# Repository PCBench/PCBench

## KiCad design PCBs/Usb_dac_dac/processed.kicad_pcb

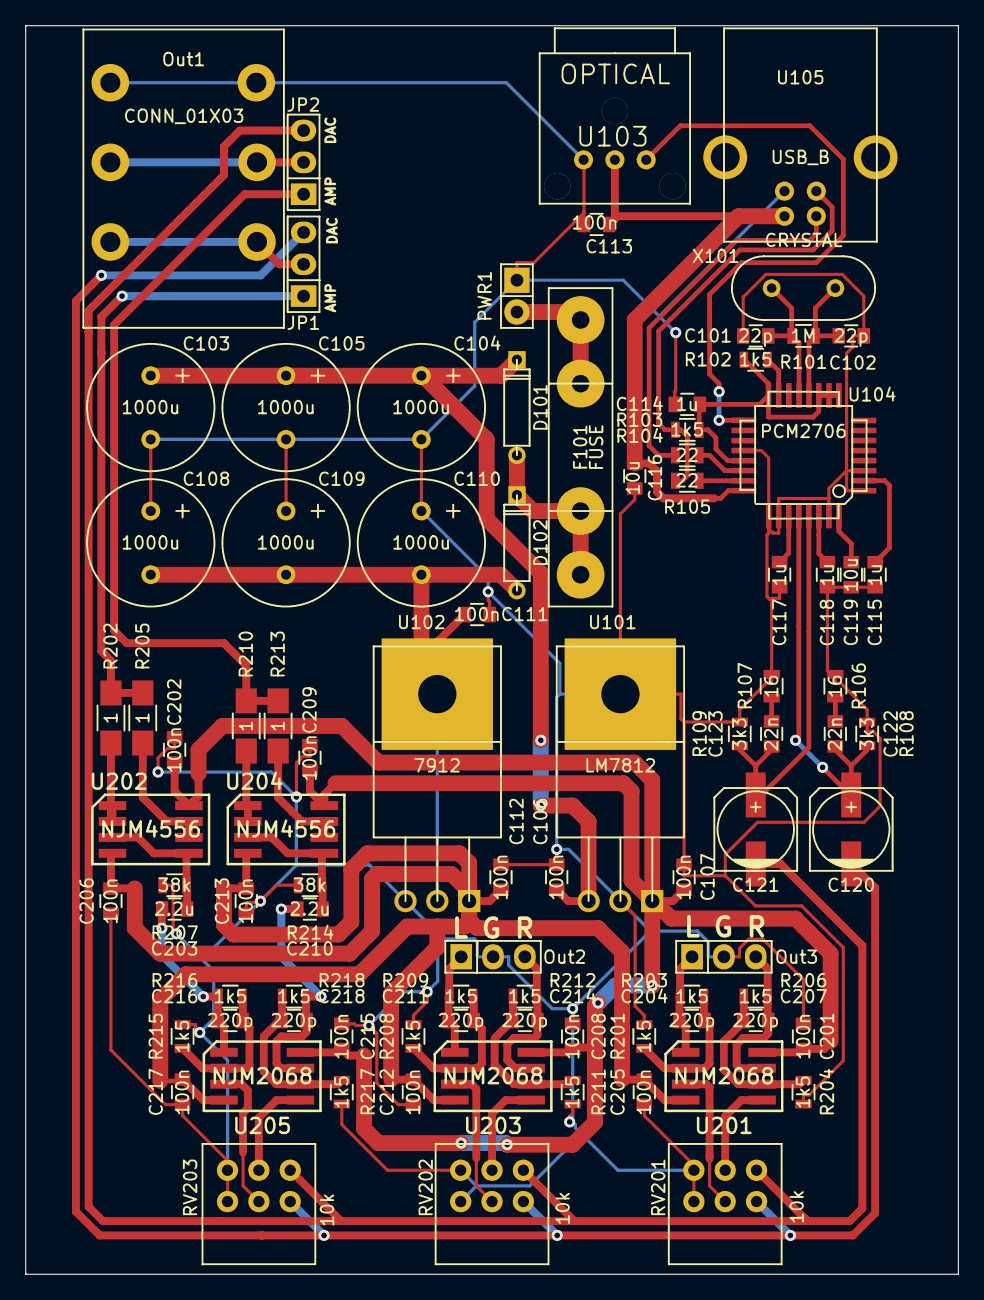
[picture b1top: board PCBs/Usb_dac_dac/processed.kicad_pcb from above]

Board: 2 copper layers, 74.4 x 99.6 mm, 91 parts (0 on the bottom side), 55 nets.

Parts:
C101, C102: 22p; C_0805
C103, C104, C105, C108, C109, C110: 1000u; Elko_vert_20x10mm_RM5
C106, C107, C111, C112, C113, C201, C202, C205, C206, C208, C209, C212, C213, C215, C217: 100n; C_0805
C114, C115, C117, C118: 1u; C_0805
C116, C119: 10u; C_0805
C120, C121: 100u; c_elec_6.3x5.3
C122, C123: 22n; C_0805
C203, C210: 2.2u; C_0805
C204, C207, C211, C214, C216, C218: 220p; C_0805
D101, D102: DIODE; D3
F101: FUSE; FUSE5-20
JP1, JP2: CONN_01X03; Pin_Header_Straight_1x03
Out1: CONN_01X03; SIKA
Out2, Out3: CONN_01X03; Pin_Header_Straight_1x03
PWR1: CONN_01X02; Pin_Header_Straight_1x02
R101: 1M; R_0805
R102, R103, R201, R203, R204, R206, R208, R209, R211, R212, R215, R216, R217, R218: 1k5; R_0805
R104, R105: 22; R_0805
R106, R107: 16; R_0805
R108, R109: 3k3; R_0805
R202, R205, R210, R213: 1; R_1206_HandSoldering
R207, R214: 38k; R_0805
RV201, RV202, RV203: 10k; RK097
U101: LM7812; TO220
U102: 7912; TO220
U103: OPTICAL; KFOX
U104: PCM2706; TQFP-32
U105: USB_B
U201, U203, U205: NJM2068; SOIC 8
U202, U204: NJM4556; SOIC 8
X101: CRYSTAL; HC-49V

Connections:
3V3: C114.2, R102.2, R103.2, U104.9, U104.10, U104.11, U104.16, U104.21
+5V: C113.2, C116.1, U103.2, U104.24, U105.1
+12V: C107.1, C201.2, C202.2, C208.2, C209.2, C215.2, U101.3, U201.8, U202.8, U203.8, U204.8, U205.8
-12V: C112.2, C205.2, C206.2, C212.2, C213.2, C217.2, U102.3, U201.4, U202.4, U203.4, U204.4, U205.4
/Buffers/Left out 1: JP1.1, R202.2, R205.2
/Buffers/Left out 2: C211.2, Out2.1, R209.2, U203.1
/Buffers/Left out 3: C204.2, Out3.1, R203.2, U201.1
/Buffers/Left_in: C120.2, JP1.3, RV201.3, RV202.3, RV203.3
/Buffers/Right out 1: JP2.1, R210.2, R213.2
/Buffers/Right out 2: C214.2, Out2.3, R212.2, U203.7
/Buffers/Right out 3: C207.2, Out3.3, R206.2, U201.7
/Buffers/Right_in: C121.2, JP2.3, RV201.6, RV202.6, RV203.6
AGND: C101.2, C102.2, C103.2, C104.2, C105.2, C106.2, C107.2, C108.1, C109.1, C110.1, C111.1, C112.1, C113.1, C114.1, C115.2, C116.2, C117.2, C118.2, C119.2, C201.1, C202.1, C205.1, C206.1, C208.1, C209.1, C212.1, C213.1, C215.1, C217.1, Out1.1, Out2.2, Out3.2, PWR1.1, R106.2, R107.2, R108.2, R109.2, R201.2, R204.2, R207.2, R208.2, R211.2, R214.2, R215.2, R217.2, RV201.1, RV201.4, RV202.1, RV202.4, RV203.1, RV203.4, U101.2, U102.1, U103.1, U104.1, U104.3, U104.20, U104.25, U104.26, U104.31, U105.4
unnamed: C101.1, R101.2, U104.13, X101.2
unnamed: C102.1, R101.1, U104.12, X101.1
unnamed: C103.1, C104.1, C105.1, C106.1, D101.2, U101.1
unnamed: C108.2, C109.2, C110.2, C111.2, D102.1, U102.2
unnamed: C115.1, U104.2
unnamed: C117.1, U104.27
unnamed: C118.1, U104.30
unnamed: C119.1, U104.32
unnamed: C120.1, C122.1, R108.1, U104.28
unnamed: C121.1, C123.1, R109.1, U104.29
unnamed: C122.2, R106.1
unnamed: C123.2, R107.1
unnamed: C203.1, C216.2, R216.2, U205.1
unnamed: C203.2, R207.1, U202.3, U202.5
unnamed: C204.1, R201.1, R203.1, U201.2
unnamed: C207.1, R204.1, R206.1, U201.6
unnamed: C210.1, C218.2, R218.2, U205.7
unnamed: C210.2, R214.1, U204.3, U204.5
unnamed: C211.1, R208.1, R209.1, U203.2
unnamed: C214.1, R211.1, R212.1, U203.6
unnamed: C216.1, R215.1, R216.1, U205.2
unnamed: C218.1, R217.1, R218.1, U205.6
unnamed: D101.1, D102.2, F101.2
unnamed: F101.1, PWR1.2
unnamed: JP1.2, Out1.3
unnamed: JP2.2, Out1.2
unnamed: R102.1, U104.15
unnamed: R103.1, R105.2, U105.3
unnamed: R104.1, U104.22
unnamed: R104.2, U105.2
unnamed: R105.1, U104.23
unnamed: R202.1, U202.1, U202.2
unnamed: R205.1, U202.6, U202.7
unnamed: R210.1, U204.1, U204.2
unnamed: R213.1, U204.6, U204.7
unnamed: RV201.2, U201.3
unnamed: RV201.5, U201.5
unnamed: RV202.2, U203.3
unnamed: RV202.5, U203.5
unnamed: RV203.2, U205.3
unnamed: RV203.5, U205.5
unnamed: U103.3, U104.17

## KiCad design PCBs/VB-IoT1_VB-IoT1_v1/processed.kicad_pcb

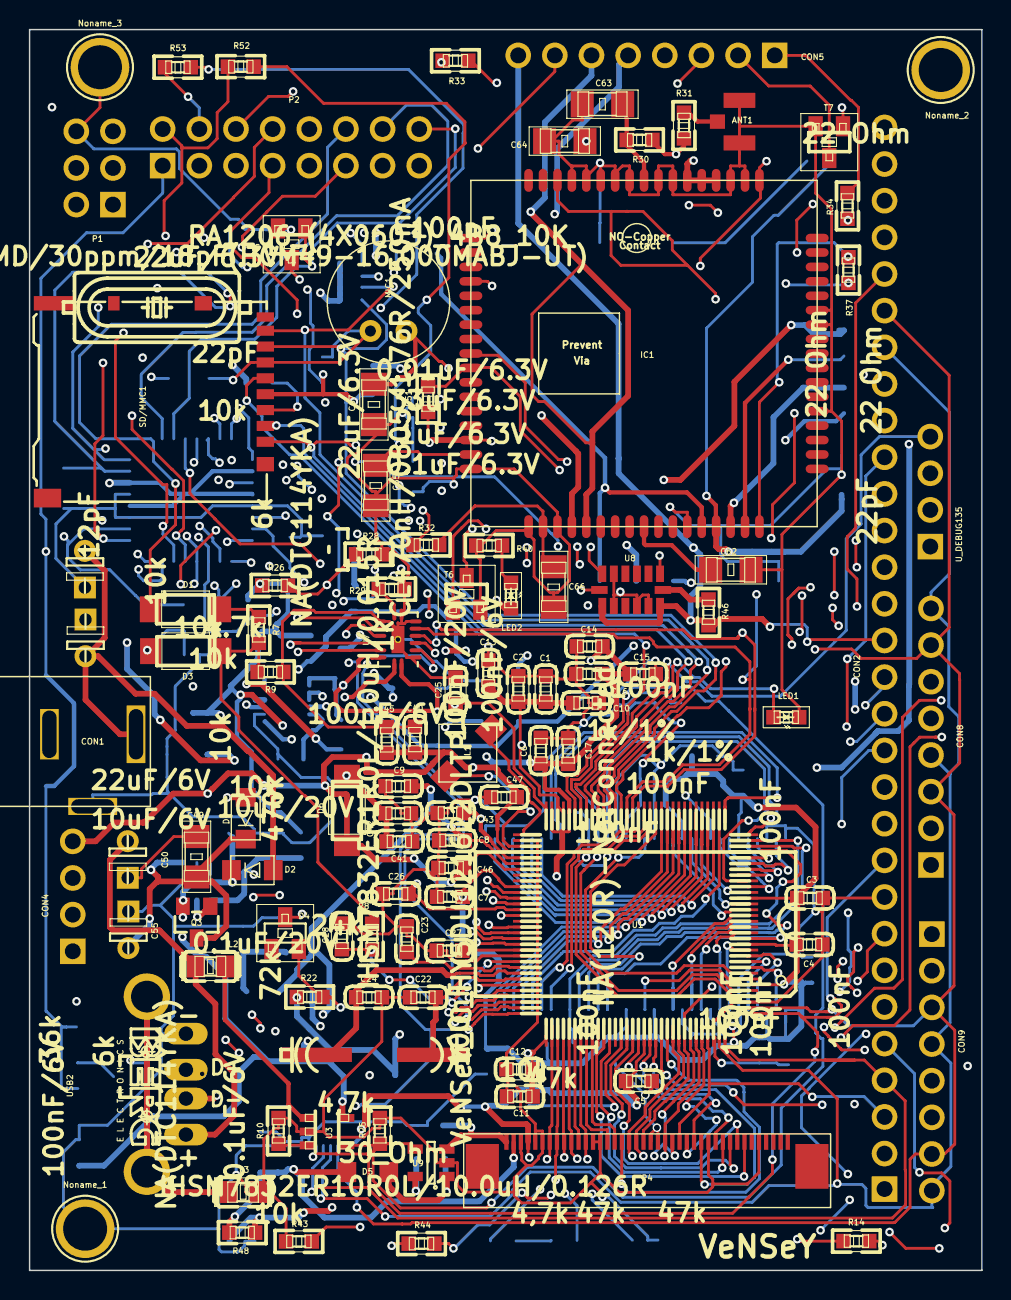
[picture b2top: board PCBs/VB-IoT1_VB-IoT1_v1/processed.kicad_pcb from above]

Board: 4 copper layers, 66.0 x 86.0 mm, 178 parts (0 on the bottom side), 195 nets.

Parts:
ANT1: 1909763-1; U.FL_CON_1909763-1
C1, C2, C3, C4, C5, C6, C11, C15, C19, C23, C25, C26, C43, C47: 0.1uF/6.3V; RCL_C0603_DWS
C7, C12, C16, C20, C27, C42, C45: 1uF/6.3V; RCL_C0603_DWS
C8, C29, C44: 22uF/6.3V; RCL_C0603_DWS
C9: 0.1uF; RCL_C0603_DWS
C10, C14, C18, C46: 0.01uF/6.3V; RCL_C0603_DWS
C13, C17, C21, C28, C40, C41: 33uF/6.3V; RCL_C0603_DWS
C22, C24: 10pF; RCL_C0603_DWS
C30, C31, C32, C33, C34, C35, C36, C37, C38, C39: 100nF; RCL_C0603_DWS
C48, C62, C65, C70, C71: 100nF/6V; RCL_C1206
C49, C52: 10uF/20V; RCL_C1206
C50: 100uF/16V/105C; RCL_E2_5-6_3
C51: 0.1uF/6V; RCL_C1206
C53, C54, C55: 220uF/10V/105C; RCL_E2_5-6_3
C56: 0.1uF/20V; RCL_C1206
C57: 10uF/6V; RCL_C1206
C58: 22uF/6V; RCL_C1206
C59: 100nF/20V; RCL_C1206
C60: 12pF; RCL_C1206
C61, C69: 22pF; RCL_C1206
C63, C64: --nF; RCL_C1206
C66, C67: 33pF; RCL_C1206
C68: 100nF; RCL_C1206
CON1: YDJ-1136; YDJ-1134-36
CON2: NA(HN1X30); PENKO_HN1X30
CON4: PENKO_CON4HN1X4; PENKO_HN1X4
CON5, CON8, CON9: PENKO_CON8HN1X8; PENKO_HN1X8
D1, D3, D6: 1N5819/SS14; GOGO_MLL-41
D2, D5, D7: SS2FL3; DO-219AB-SMF
D4: BAT54C; SEMICON-SMD-IPC_SOT23C
IC1: SIM900
IC2: ATMEGA328P-A; TQFP-32_7x7mm_Pitch0.8mm
L1: CDRH3D28NP-150N
L2, L3: FB0805/600R/2A; RCL_L0805_5MIL_DWS
L4: CL470nH/0805/1.76R/250mA; RCL_L0805_5MIL_DWS
L5: IHSM7832ER10R0L/10.0uH/0.126R; RCL_L0805_5MIL_DWS
L6: IHSM7832ER1R0L/1.0uH/0.015R; RCL_L0805_5MIL_DWS
LED1, LED2: GREEN(0603); DOUBLE-SIDE_LED-0603
MIC1: CEM-C9745JAD462P2.54R; ELECTRET_MIC
Noname_1, Noname_2, Noname_3: 1pin
P1: CONN_02X03; PENKO_HN2x3
P2: CONN_02X08; PENKO_HN2x8
P3: MOLEX_503480-0800; molex8-FCP
P4: TE_CONNECTIVITY_4-1734592-0; teConn40-FCP
Q1: Q24.000MHz/HC-49SM/SMD/20ppm/20pF; CRYSTAL_HC49_SMD2_THIN
Q2: Q16.000MHz/HCM49/SMD/30ppm/18pF(HCM49-16.000MABJ-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; CRYSTAL_HC49_SMD2_THIN
Q3: FDN306P; SUPERSOT-3
Q4: SQ2309ES; SOT23GDS
R1, R47: 6k; RCL_R0603_5MIL_DWS
R2: 36k; RCL_R0603_5MIL_DWS
R3, R4, R5, R7, R10, R16, R20, R21, R25, R39, R45, R46: 10k; RCL_R0603_5MIL_DWS
R6, R22: 4.7k; RCL_R0603_5MIL_DWS
R8, R40, R41: 1k; RCL_R0603_5MIL_DWS
R9: 100k; RCL_R0603_5MIL_DWS
R11, R12: 4,7k; RCL_R0603_5MIL_DWS
R13, R15, R42, R43, R44: 47k; RCL_R0603_5MIL_DWS
R14: NA(47k); RCL_R0603_5MIL_DWS
R17: NA(120R)-NotConnected; RCL_R0603_5MIL_DWS
R18, R19: 1k/1%; RCL_R0603_5MIL_DWS
R23: 24k; RCL_R0603_5MIL_DWS
R24: 72k; RCL_R0603_5MIL_DWS
R26: 768k; RCL_R0603_5MIL_DWS
R27: 470k; RCL_R0603_5MIL_DWS
R28: 137k; RCL_R0603_5MIL_DWS
R29, R51: 1K; RCL_R0603_5MIL_DWS
R30, R31: 0 Ohm; RCL_R0603_5MIL_DWS
R32: 33 Ohm; RCL_R0603_5MIL_DWS
R33, R34: 300 Ohm; RCL_R0603_5MIL_DWS
R35, R36, R38: 22 Ohm; RCL_R0603_5MIL_DWS
R37: 10K; RCL_R0603_5MIL_DWS
R48: 150k; RCL_R0603_5MIL_DWS
R50: 30_Ohm; RCL_R0603_5MIL_DWS
R52, R53: 2k; RCL_R0603_5MIL_DWS
R-MAT1: RA1206_(4X0603)_4B8_10K; OLIMEX_DISCRET_R_MATRIX_4
SD/MMC1: DM3AT-SF-PEJM5; HIROSE-MICROSD-DM3AT-SF_nooli
SIM1: Molex912283001; 91228-3001
T1, T5, T6, T7, T8: NA(DTC114YKA); OLIMEX_DISCRET_SOT-23
U1: MCIMX233CAG4C; OLIMEX_IC_TQFP128LD
U2: VeNSeY_IC_HY5DU121622DLTP-J; OLIMEX_IC_66TSOP-II
U3: SY6280; OLIMEX_IC_SOT23-5
U4: LTC4412
U5: TPS63020; VSON-14
U6: LM317AEMP; SOT223
U7: 74AVC4TD245; DHVQFN-16_2.5x3.5mm_Pitch0.5mm
U8: ADXL345; LGA14
U9: FAN5331SX; SOT-23-5
USB2: OLIMEX_CONNECTORS_USB_SHIELD; OLIMEX_CONNECTORS_USB_PN87520_DEV_PTH
U_DEBUG135: HN1X4; PENKO_HN1X4

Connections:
3V3_MODEM: C71.2, CON8.2, CON8.6, CON9.2, CON9.6, IC1.55, IC1.56, IC1.57, L5.2, LED2.A, Q4.D, R33.2, R34.2, U9.5
3V3_MODEM_ON: IC2.12, T8.1
3v3_Perm+: C58.1, C70.1, CON2.16, CON5.8, IC2.4, IC2.6, IC2.18, IC2.20, P1.2, Q4.S, R4.1, R5.1, R26.2, R27.2, R39.2, R46.1, U5.4, U8.1, U8.6
5V_Converter_IN: C48.1, C52.1, D2.1, Q3.S, U3.5, U4.6, U6.3
5V_IN: C8.1, C9.1, C56.1, CON2.1, R23.2, U1.102, U6.2
/A0: U1.76, U2.29
/A1: U1.75, U2.30
/A2: U1.74, U2.31
/A3: U1.73, U2.32
/A4: U1.72, U2.35
/A5: U1.71, U2.36
/A6: U1.70, U2.37
/A7: U1.69, U2.38
/A8: U1.68, U2.39
/A9: U1.67, U2.40
/A10: U1.66, U2.28
/A11: U1.65, U2.41
/A12: U1.64, U2.42
/ATM_ADC1_PC1: IC2.24, P2.11
/ATM_ADC2_PC2: IC2.25, P2.13
/ATM_ADC3_PC3: IC2.26, P2.15
/ATM_ADC6_BattStatus: IC2.19, P2.1, R1.2, R2.1
/ATM_ADC7: IC2.22, P2.7
/ATM_PD4: IC2.2, P2.10, R3.2
/ATM_PD6: IC2.10, P2.14
/AdapterIN+: C53.+, C54.+, CON1.1, D2.2
/BA0: U1.79, U2.26
/BA1: U1.80, U2.27
/CASN: U1.61, U2.22
/CKE: U1.78, U2.44
/CLK: R17.2, U1.36, U2.45
/CLKN: R17.1, U1.37, U2.46
/CS: R16.1, U1.63, U2.24
/D0: U1.41, U2.2
/D1: U1.43, U2.4
/D2: U1.42, U2.5
/D3: U1.44, U2.7
/D4: U1.47, U2.8
/D5: U1.48, U2.10
/D6: U1.49, U2.11
/D7: U1.50, U2.13
/D8: U1.51, U2.54
/D9: U1.52, U2.56
/D10: U1.54, U2.57
/D11: U1.55, U2.59
/D12: U1.57, U2.60
/D13: U1.58, U2.62
/D14: U1.60, U2.63
/D15: U1.59, U2.65
/DQM0: U1.46, U2.20
/DQM1: U1.56, U2.47
/DQS0: U1.39, U2.16
/DQS1: U1.40, U2.51
/HPL: CON2.7, U1.113
/HPR: CON2.8, U1.109
/HP_VGND: CON2.18, U1.111
/LIN1_INL: CON2.19, U1.115
/LIN1_INR: CON2.20, U1.114
/MIC_P: C66.2, IC1.19, R32.1
/MODEM_PWRKEY: IC1.1, T5.3
/MODEM_RI: IC1.4, U7.12
/MODEM_RXD: IC1.10, R51.1, U7.13
/MODEM_STATUS: IC1.66, T6.1
/MODEM_TXD: IC1.9, U7.14
/NETLIGHT: IC1.52, T7.1, U7.11
/PIN1/LCD_D00: P4.7, R44.2, U1.2
/PIN2/LCD_D01: P4.8, R43.1, U1.3
/PIN3/LCD_D02: P4.9, R42.1, U1.4
/PIN4/LCD_D03: P4.10, R13.2, U1.5
/PIN5/LCD_D04: P4.11, U1.6
/PIN6/LCD_D05: P4.12, R14.1, U1.7
/PIN7/LCD_D06: P4.15, U1.8
/PIN8/LCD_D07: P4.16, U1.9
/PIN9/LCD_D08/SSP2_MISO: P4.17, U1.22
/PIN10/LCD_D09: CON2.11, P4.18, U1.23
/PIN11/LCD_D10: CON2.12, P4.19, U1.24
/PIN12/LCD_D11: CON2.13, P4.20, U1.25
/PIN13/LCD_D12: CON2.14, P4.23, U1.27
/PIN14/LCD_D13: CON2.15, P4.24, U1.26
/PIN15/LCD_D14: CON2.3, P4.25, U1.29
/PIN16/LCD_D15: CON2.17, P4.26, U1.28
/PIN17/LCD_D16: P4.27, U1.19
/PIN18/LCD_D17/USB_EN: P4.28, U1.20
/PIN19/LCD_DOTCLK: P4.30, U1.17
/PIN20/LCD_VSYNC: P4.33, U1.16
/PIN21/LCD_HSYNC/I2C_SDA: P4.32, U1.15
/PIN22/LCD_EN/I2C_SCL: P4.34, U1.11
/PIN23/LCD_DISP: P4.31, U1.12
/PIN25/LCD_RS: R15.2, U1.14
/PIN32/LRADC1: CON2.23, U1.107
/PIN33/LRADC0: CON2.22, U1.108
/PIN34/MIC: CON2.21, U1.116
/PSWITCH: C28.2, R8.2, U1.119
/RASN: U1.62, U2.23
/RF_ANT: C63.2, IC1.60, R30.1
/SD_VCC: C29.2, C44.2, L4.2, SD/MMC1.4
/SIM_CLK: IC1.32, R36.2
/SIM_DATA: C69.2, IC1.31, R38.2
/SIM_PRESENCE: IC1.34, R37.1, SIM1.C8
/SIM_RST: IC1.33, R35.2
/SIM_VDD: C68.2, IC1.30, SIM1.C1
/VDD_EXT: IC1.15, R37.2, R51.2, U7.16
/WEN: U1.77, U2.21
/XTALI: C22.2, Q1.2, U1.122
/XTALO: C24.2, Q1.1, U1.121
ADXL_INT: IC2.14, T1.1, U8.8
ATM_FALL_INTO_SPECIAL_STATE1: CON2.26, IC2.32, P2.6, U1.21
ATM_FALL_INTO_SPECIAL_STATE2: IC2.1, P2.8
ATM_MISO: IC2.16, P1.1
ATM_MOSI: IC2.15, P1.4
ATM_RESET: IC2.29, P1.5
ATM_RXD: IC2.30, P2.2, R52.1
ATM_SCK: IC2.17, P1.3
ATM_TXD: IC2.31, P2.4, R53.1
AdapterStatus_IN: IC2.13, R27.1, U4.4
BatteryIN+: C40.2, C45.2, C46.2, C47.2, C57.1, CON2.30, CON4.4, D6.A, R1.1, U1.100, U1.103, U5.10, U5.11
BatteryIN-: ANT1.2, C1.1, C2.1, C3.1, C4.1, C5.1, C6.1, C7.2, C8.2, C9.2, C10.1, C11.1, C12.1, C13.1, C14.1, C15.1, C16.1, C17.1, C18.1, C19.1, C20.1, C21.1, C22.1, C23.1, C24.1, C25.1, C26.1, C27.1, C28.1, C29.1, C30.1, C31.1, C32.1, C33.1, C34.1, C35.1, C36.1, C37.1, C39.1, C40.1, C41.1, C42.1, C43.1, C44.1, C45.1, C46.1, C47.1, C48.2, C49.2, C50.-, C51.2, C52.2, C53.-, C54.-, C55.-, C56.2, C57.2, C58.2, C59.2, C60.2, C61.2, C62.2, C63.1, C64.1, C65.2, C66.1, C67.1, C68.1, C69.1, C71.1, CON1.2, CON1.3, CON2.2, CON2.9, CON4.2, CON4.3, CON8.1, CON8.5, CON9.1, CON9.5, IC1.17, IC1.18, IC1.20, IC1.29, IC1.39, IC1.45, IC1.46, IC1.53, IC1.54, IC1.58, IC1.59, IC1.61, IC1.62, IC1.63, IC1.64, IC1.65, IC2.3, IC2.5, IC2.21, L3.2, LED1.C, MIC1.2, Noname_1.1, Noname_2.1, Noname_3.1, P1.6, P3.1, P3.2, P4.3, P4.5, P4.6, P4.13, P4.14, P4.21, P4.22, P4.29, P4.36, R6.2, R9.1, R10.1, R14.2, R19.1, R20.2, R24.1, R25.1, R28.1, R29.2, R40.1, R42.2, R43.2, R45.2, R47.2, R50.2, SD/MMC1.6, SIM1.C4, SIM1.C5, T1.2, T5.2, T6.2, T7.2, T8.2, U1.30, U1.35, U1.98, U1.105, U1.112, U1.118, U2.6, U2.12, U2.34, U2.48, U2.52, U2.58, U2.64, U2.66, U3.2, U4.2, U4.3, U5.2, U7.2, U7.7, U7.8, U7.10, U7.17, U8.2, U8.4, U8.5, U8.12, U9.2, USB2.4, U_DEBUG135.3
DEBUG: U1.89, U_DEBUG135.4
IMX_ATM_SCL: CON2.25, CON8.3, CON8.7, CON9.3, CON9.7, IC2.28, P2.5, P3.6, R5.2, U1.34, U8.14
IMX_ATM_SDA: CON2.24, CON8.4, CON8.8, CON9.4, CON9.8, IC2.27, P2.3, P3.5, R4.2, U1.31, U8.13
IMX_PSWITCH: D3.A, R3.1, R6.1
IMX_RECOVERY: D1.A, IC2.9, P2.12
LCD_LED+: C51.1, D5.1, P4.2, R48.1
LCD_LED-: P4.1, R20.1, R48.2, R50.1, U9.3
LCD_USB_EN: R25.2, U1.91, U3.4, U9.4
MODEM_NET_ON: CON2.28, U1.82, U7.6
MODEM_PWRKEY_SIG: IC2.11, P2.16, T5.1
MODEM_RINGING: CON2.27, U1.81, U7.5
MODEM_STATUS_N: CON5.4, T6.3
MODEM_STATUS_P: CON5.3, R33.1
NETLIGHT_LED_N: CON5.2, T7.3
NETLIGHT_LED_P: CON5.1, R34.1
unnamed: ANT1.1, R31.2
unnamed: C27.2, U1.117
unnamed: C38.2, C39.2, R18.1, R19.2, U2.49
unnamed: C49.1, C55.+, D7.1, Q3.D, U4.1
unnamed: C50.+, L2.2, USB2.1
unnamed: C59.1, U5.1, U5.12
unnamed: C60.1, IC2.7, Q2.2
unnamed: C61.1, IC2.8, Q2.1
unnamed: C62.1, IC1.26
unnamed: C64.2, R30.2, R31.1
unnamed: C65.1, IC1.16
unnamed: C67.2, MIC1.1, R32.2
unnamed: C70.2, Q4.G, R39.1, R41.2
unnamed: D1.K, R7.2
unnamed: D3.K, R7.1, R8.1, R9.2
unnamed: D4.3, U_DEBUG135.1
unnamed: D5.2, L5.1, U9.1
unnamed: L1.1, U1.97
unnamed: L1.2, U1.99
unnamed: L2.1, U3.1
unnamed: L3.1, USB2.P$1, USB2.P$2
unnamed: L6.1, U5.8, U5.9
unnamed: L6.2, U5.6, U5.7
unnamed: LED2.C, R40.2
unnamed: Q3.G, U4.5
unnamed: R2.2, T1.3
unnamed: R10.2, U3.3
unnamed: R11.2, R13.1
unnamed: R12.2, R44.1
unnamed: R23.1, R24.2, U6.1
unnamed: R26.1, R28.2, U5.3
unnamed: R29.1, U7.9
unnamed: R35.1, SIM1.C2
unnamed: R36.1, SIM1.C3
unnamed: R38.1, SIM1.C7
unnamed: R41.1, T8.3
unnamed: R45.1, U5.13
unnamed: R46.2, U8.7
PHOTO_TRAN_N: CON5.7, IC2.23, P2.9, R47.1
RX_FROM_MODEM: CON2.5, R52.2, U1.128, U7.3
SPK_CON_N: CON5.6, IC1.22
SPK_CON_P: CON5.5, IC1.21
SSP1_CMD: R21.1, SD/MMC1.3, U1.83
SSP1_DATA0: R-MAT1.1.2, SD/MMC1.7, U1.84
SSP1_DATA1: R-MAT1.2.2, SD/MMC1.8, U1.85
SSP1_DATA2: R-MAT1.3.2, SD/MMC1.1, U1.86
SSP1_DATA3: R-MAT1.4.2, SD/MMC1.2, U1.87
SSP1_SCK: SD/MMC1.5, U1.90
Solar+: CON4.1, D7.2
TOUCH_INT: CON2.4, P3.4, U1.32
TOUCH_RST: CON2.10, P3.3, U1.33
TX_TO_MODEM: CON2.6, R53.2, U1.127, U7.4
USB_DM: U1.123, USB2.2
USB_DP: U1.124, USB2.3
VDD4P2: C41.2, C42.2, C43.2, D6.K, U1.101
imx1V0_OUT: C23.2, U1.120
imx1V2_OUT: C1.2, C2.2, C10.2, C11.2, C12.2, C13.2, U1.1, U1.93, U1.94
imx1V8_OUT: C18.2, C19.2, C20.2, C21.2, C25.2, C26.2, U1.96, U1.110
imx2V5_OUT: C3.2, C4.2, C7.1, C30.2, C31.2, C32.2, C33.2, C34.2, C35.2, C36.2, C37.2, C38.1, R16.2, R18.2, U1.38, U1.45, U1.53, U1.106, U2.1, U2.3, U2.9, U2.15, U2.18, U2.33, U2.55, U2.61
imx3V3_OUT: C5.2, C6.2, C14.2, C15.2, C16.2, C17.2, CON2.29, L4.1, P3.7, P3.8, P4.4, R11.1, R12.1, R15.1, R21.2, R22.1, R-MAT1.1.1, R-MAT1.2.1, R-MAT1.3.1, R-MAT1.4.1, U1.18, U1.92, U1.95, U7.1, U7.15
imx_LED: LED1.A, U1.88
imx_RXD: D4.2, R22.2, U1.125
imx_TXD: U1.126, U_DEBUG135.2

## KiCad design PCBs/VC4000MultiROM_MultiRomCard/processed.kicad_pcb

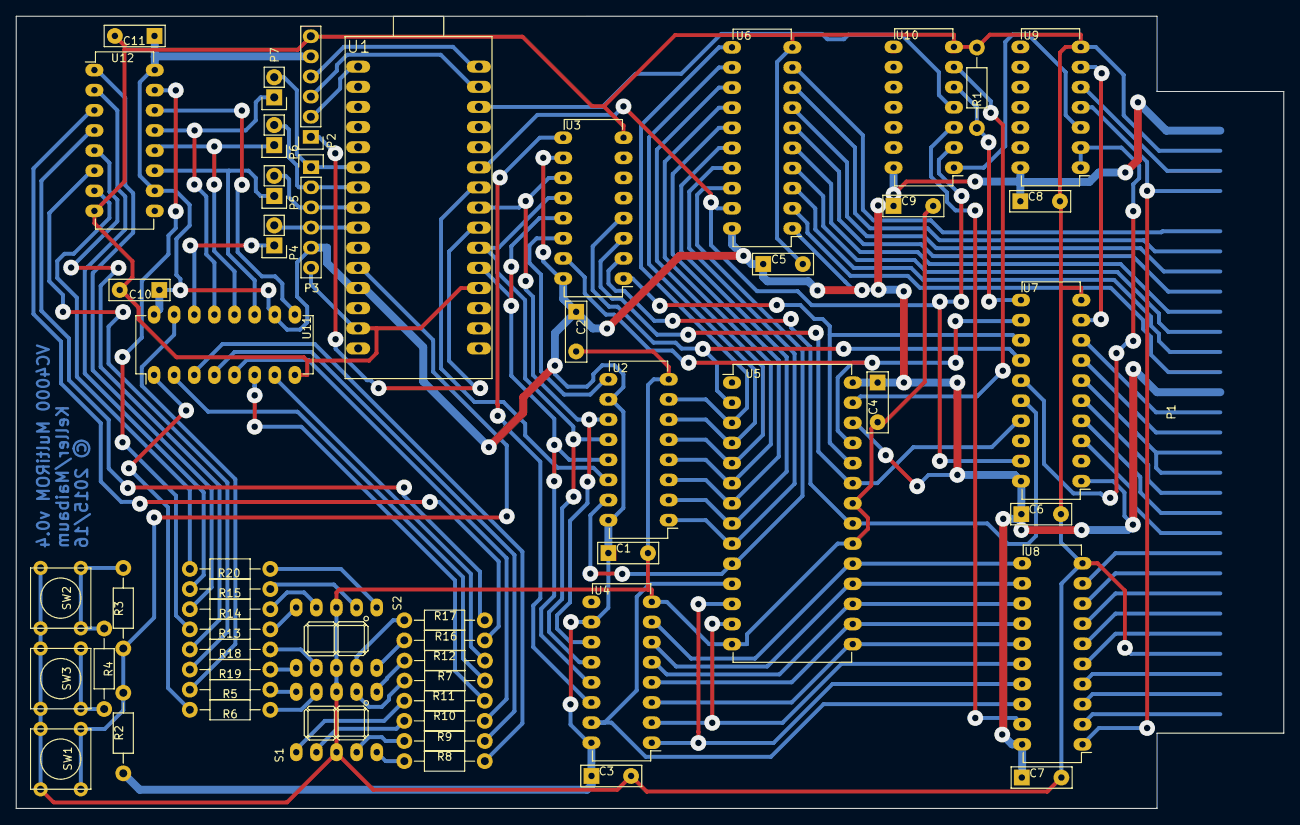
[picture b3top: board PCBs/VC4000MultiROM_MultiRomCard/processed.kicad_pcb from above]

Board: 2 copper layers, 160.0 x 100.0 mm, 55 parts (0 on the bottom side), 109 nets.

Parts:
C1, C2, C3, C4, C5, C6, C7, C8, C9, C10, C11: .1uF; C_Rect_L7_W2_P5_DIY
P1: VC4000_Cartridge_Bus; VC4000_CartridgeBus
P2: MicroSD_Breakout; Pin_Header_Straight_1x06
P3: DISPLAY; Pin_Header_Straight_1x06
P4: JUMPER1; Pin_Header_Straight_1x02
P5: JUMPER2; Pin_Header_Straight_1x02
P6: JUMPER3; Pin_Header_Straight_1x02
P7: JUMPER4; Pin_Header_Straight_1x02
R1: 10k; Resistor_Horizontal_RM10mm
R2: 2k2; Resistor_Horizontal_RM10mm
R3, R5, R6, R7, R8, R9, R10, R11, R12, R13, R14, R15, R16, R17, R18, R19, R20: 330; Resistor_Horizontal_RM10mm
R4: 1k; Resistor_Horizontal_RM10mm
S1, S2: 7SEGM_KB_SC39-11; 7_Segment_Display_KB_13_10mm
SW1: UP; SW_PUSH_SMALL
SW2: DOWN; SW_PUSH_SMALL
SW3: SELECT; SW_PUSH_SMALL
U1: Arduino_Nano
U2, U3, U4, U11, U12: 74HC595; DIP-16_W7.62mm_LongPads
U5: 6264; DIP-28_W15.24mm_LongPads
U6, U7, U8: 74HC245; DIP-20_W7.62mm_LongPads
U9: 74HC00; DIP-14_W7.62mm_LongPads
U10: 74HC32; DIP-14_W7.62mm_LongPads

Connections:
/A0: U2.15, U5.10, U6.18
/A1: U2.1, U5.9, U6.17
/A2: U2.2, U5.8, U6.16
/A3: U2.3, U5.7, U6.15
/A4: U2.4, U5.6, U6.14
/A5: U2.5, U5.5, U6.13
/A6: U2.6, U5.4, U6.12
/A7: U2.7, U5.3, U6.11
/A8: U3.15, U5.25, U7.12
/A9: U3.1, U5.24, U7.13
/A10: U3.2, U5.21, U7.16
/A11: U3.3, U5.23, U7.17
/A12: U3.4, U5.2, U7.14
/CE1: P1.12, U7.5
/D0: U4.15, U5.11, U8.18
/D1: U4.1, U5.12, U8.17
/D2: U4.2, U5.13, U8.16
/D3: U4.3, U5.15, U8.15
/D4: U4.4, U5.16, U8.14
/D5: U4.5, U5.17, U8.13
/D6: U4.6, U5.18, U8.12
/D7: U4.7, U5.19, U8.11
/EA0: P1.18, U6.2
/EA1: P1.19, U6.3
/EA2: P1.20, U6.4
/EA3: P1.21, U6.5
/EA4: P1.22, U6.6
/EA5: P1.23, U6.7
/EA6: P1.24, U6.8
/EA7: P1.25, U6.9
/EA8: P1.16, U7.8
/EA9: P1.15, U7.7
/EA10: P1.11, U7.4
/EA11: P1.10, U7.3
/EA12: P1.13, P1.14, U7.6
/ED0: P1.1, U8.2
/ED1: P1.2, U8.3
/ED2: P1.3, U8.4
/ED3: P1.5, U8.5
/ED4: P1.6, U8.6
/ED5: P1.7, U8.7
/ED6: P1.8, U8.8
/ED7: P1.9, U8.9
/RW: P1.27, U8.1, U9.4
/WRP: P1.28, U9.5
CEDBUS: U8.19, U10.3
GND: C1.2, C2.2, C3.2, C4.2, C5.2, C6.2, C7.2, C8.2, C9.2, C10.2, C11.2, P1.4, P1.29, P2.6, P3.6, R1.2, S1.3, S1.8, S2.3, S2.8, SW1.2, SW2.2, SW3.2, U1.4, U1.29, U2.8, U3.8, U4.8, U5.14, U5.20, U5.22, U6.10, U7.10, U8.10, U9.7, U10.7, U11.8, U12.8
unnamed: P2.1, U1.7
unnamed: P2.2, U1.16
unnamed: P2.3, U1.14
unnamed: P2.4, U1.15
unnamed: P3.1, P7.2, U1.21
unnamed: P3.2, P6.2, U1.22
unnamed: P3.3, P5.2, U1.23
unnamed: P3.4, P4.2, U1.24
unnamed: P4.1, U11.14
unnamed: P5.1, U11.11, U12.11
unnamed: P6.1, U11.12, U12.12
unnamed: P7.1, U11.13, U12.13
unnamed: R1.1, U7.11, U10.5
unnamed: R2.1, R3.2, SW1.1, U1.26
unnamed: R3.1, R4.2, SW2.1
unnamed: R4.1, SW3.1
unnamed: R5.1, S1.10
unnamed: R5.2, U11.15
unnamed: R6.1, S1.9
unnamed: R6.2, U11.1
unnamed: R7.1, S1.7
unnamed: R7.2, U11.2
unnamed: R8.1, S1.5
unnamed: R8.2, U11.3
unnamed: R9.1, S1.4
unnamed: R9.2, U11.4
unnamed: R10.1, S1.2
unnamed: R10.2, U11.5
unnamed: R11.1, S1.1
unnamed: R11.2, U11.6
unnamed: R12.1, S1.6
unnamed: R12.2, U11.7
unnamed: R13.1, S2.10
unnamed: R13.2, U12.15
unnamed: R14.1, S2.9
unnamed: R14.2, U12.1
unnamed: R15.1, S2.7
unnamed: R15.2, U12.2
unnamed: R16.1, S2.5
unnamed: R16.2, U12.3
unnamed: R17.1, S2.4
unnamed: R17.2, U12.4
unnamed: R18.1, S2.2
unnamed: R18.2, U12.5
unnamed: R19.1, S2.1
unnamed: R19.2, U12.6
unnamed: R20.1, S2.6
unnamed: R20.2, U12.7
unnamed: U1.5, U2.13, U3.13, U4.13
unnamed: U1.6, U2.12, U3.12, U4.12
unnamed: U1.8, U2.11, U3.11, U4.11
unnamed: U1.9, U2.14
unnamed: U2.9, U3.14
unnamed: U3.9, U4.14
unnamed: U7.15, U9.1, U9.2
unnamed: U9.3, U10.1
unnamed: U5.27, U10.6
unnamed: U11.9, U12.14
OEVCBUS: U1.10, U6.19, U7.19, U10.2
VCC: C1.1, C2.1, C3.1, C4.1, C5.1, C6.1, C7.1, C8.1, C9.1, C10.1, C11.1, P1.17, P1.30, P2.5, P3.5, R2.2, U1.27, U2.10, U2.16, U3.10, U3.16, U4.10, U4.16, U5.26, U5.28, U6.1, U6.20, U7.1, U7.20, U8.20, U9.14, U10.14, U11.10, U11.16, U12.10, U12.16
WCONTROL: U7.9, U9.6
WESRAM: U1.13, U10.4

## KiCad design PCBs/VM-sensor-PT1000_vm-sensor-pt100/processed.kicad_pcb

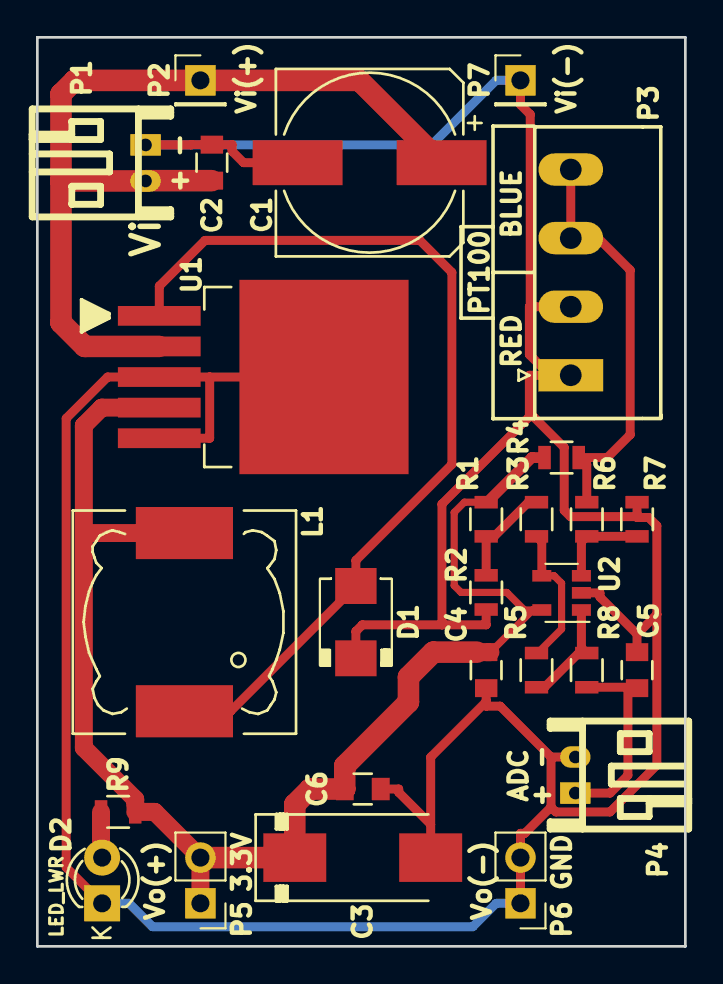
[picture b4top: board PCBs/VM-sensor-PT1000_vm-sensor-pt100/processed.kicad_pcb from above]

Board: 2 copper layers, 36.0 x 50.5 mm, 27 parts (0 on the bottom side), 11 nets.

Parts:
C1: 470uF/50v; c_elec_10x10.5
C2, C6: 10uF/16v; C_0805
C3: 330uF/16V; Tantalum_Case-D_EIA-7343-31_Hand
C4, C5: 10uF; C_0805
D1: SS34; do214aa-g
D2: LED_Small; LED-3MM
L1: 47uH/RH127-470; Choke_SMD_12x12mm_h8mm
P1: Vi; s2b-ph-kl
P2: Vin(+); Pin_Header_Straight_1x01_Pitch2.54mm
P3: PT100; Domino-PT100.pretty
P4: ADC; s2b-ph-kl
P5: Vo(+); Pin_Header_Straight_1x02_Pitch2.54mm
P6: Vo(-); Pin_Header_Straight_1x02_Pitch2.54mm
P7: Vin(-); Pin_Header_Straight_1x01_Pitch2.54mm
R1, R4: 3.3K/1%; R_0805
R2: 100R/1%; R_0805
R3, R6: 16.9K/1%; R_0805
R5, R7: 1M/1%; R_0805
R8: 1K/1%; R_0805
R9: 100R; R_0805
U1: LM2595S-3.3; TO-263-5Lead
U2: MCP601T; SOT-23-5

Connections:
+3V3: C3.1, C4.1, C6.1, L1.2, P5.1, P5.2, R1.1, R4.1, R9.1, U1.4, U2.5
/ADC: C5.1, P4.1, R8.1
/Blue: P3.3, P3.4, R4.2, R6.2
GND: C1.2, C2.2, C3.2, C4.2, C5.2, C6.2, D1.2, D2.1, P1.1, P3.1, P3.2, P4.2, P6.1, P6.2, P7.1, R2.2, R7.1, U1.3, U1.5, U2.2
unnamed: D1.1, L1.1, U1.1
unnamed: D2.2, R9.2
unnamed: R1.2, R2.1, R3.2
unnamed: R3.1, R5.1, U2.4
unnamed: R5.2, R8.2, U2.1
unnamed: R6.1, R7.2, U2.3
VCC: C1.1, C2.1, P1.2, P2.1, U1.2

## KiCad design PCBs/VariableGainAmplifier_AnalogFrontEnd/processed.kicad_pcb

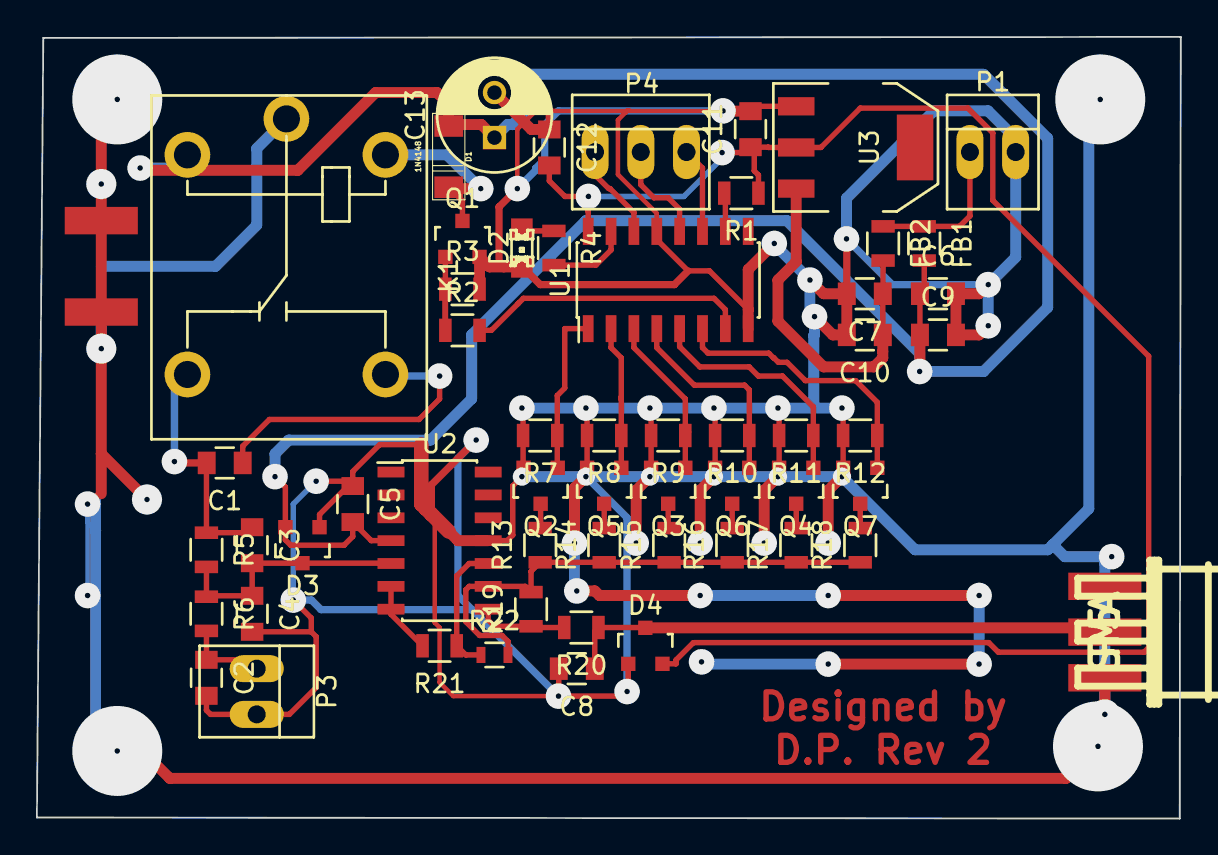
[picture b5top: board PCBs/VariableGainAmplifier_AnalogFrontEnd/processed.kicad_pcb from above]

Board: 2 copper layers, 63.5 x 43.4 mm, 57 parts (1 on the bottom side), 36 nets.

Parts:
C1, C2, C5, C6, C7, C12: 100n; C_0805
C3: 12pF; C_0805
C4: 47pF; C_0805
C8: 10p; C_0805
C9, C10, C11: 10u; C_0805
C13: 100u; C_Radial_D6.3_L11.2_P2.5
D1: 1N4148; MiniMelf
D2: LED; LED-0805
D3, D4: BAT54S; SOT-23
FB1, FB2: MH2029-300Y; Ind_0805
K1: RELAY_SONGLE_RD-XVDC-SL-C; SONGLE_SRD-XVDC-SL-C
P1: Power; PINHEAD1-2
P2, P5: SMA; CON-SMA-EDGE
P3: DAC_Offset; PINHEAD1-2
P4: ShiftReg; PINHEAD1-3
Q1: MMBT2222A; SOT-23
Q2, Q3, Q4, Q5, Q6, Q7: Si2302DS; SOT-23
R1, R3, R7, R8, R9, R10, R11, R12: 10k; R_0805
R2: 1k; R_0805
R4: 330; R_0805
R5: 840k/1%; R_0805
R6: 160k/1%; R_0805
R13, R19: 200/1%; R_0805
R14: 1M/1%; R_0805
R15: 50; R_0805
R16, R20: 22; R_0805
R17: 10; R_0805
R18: 5; R_0805
R21: 0; R_0805
R22: 100; R_0603
U1: 74HC595; SOIC-16_3.9x9.9mm_Pitch1.27mm
U2: MCP660; SOIC-14_3.9x8.7mm_Pitch1.27mm
U3: LD1117S33TR; SOT-223

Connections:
/5V: C5.2, C6.1, C9.1, C13.1, D1.1, D3.2, FB1.2, K1.1, U2.4
/5V_IN: FB1.1, FB2.1, P1.1
/AC/DC: R2.2, U1.7
/DAC_Offset: C2.1, P3.1, R6.2
/SR_RCLK: P4.2, U1.12
/SR_SER: P4.1, U1.14
/SR_SRCLK: P4.3, U1.11
/V_IN: C8.1, D4.3, P5.1, R20.1
GND: C2.2, C4.2, C5.1, C6.2, C7.2, C8.2, C9.2, C10.2, C11.2, C12.1, C13.2, D2.1, D3.1, D4.1, P1.2, P2.2, P3.2, P5.2, Q1.2, Q2.2, Q3.2, Q4.2, Q5.2, Q6.2, Q7.2, R3.2, R7.2, R8.2, R9.2, R10.2, R11.2, R12.2, U1.8, U1.13, U2.11, U3.1
unnamed: C1.1, K1.5
unnamed: C1.2, C3.1, K1.4, R5.1
unnamed: C3.2, C4.1, D3.3, R5.2, R6.1, U2.5
unnamed: C7.1, C10.1, FB2.2, U3.3
unnamed: D1.2, K1.2, Q1.3
unnamed: D2.2, R4.1
unnamed: K1.3, P2.1
unnamed: Q1.1, R2.1, R3.1
unnamed: Q2.1, R7.1, U1.1
unnamed: Q2.3, R13.2
unnamed: Q3.1, R9.1, U1.3
unnamed: Q3.3, R15.2
unnamed: Q4.1, R11.1, U1.5
unnamed: Q4.3, R17.2
unnamed: Q5.1, R8.1, U1.2
unnamed: Q5.3, R14.2
unnamed: Q6.1, R10.1, U1.4
unnamed: Q6.3, R16.2
unnamed: Q7.1, R12.1, U1.6
unnamed: Q7.3, R18.2
unnamed: R1.2, U1.10
unnamed: R4.2, U1.15
unnamed: R13.1, R14.1, R15.1, R16.1, R17.1, R18.1, R19.2, R22.2, U2.9
unnamed: R19.1, R20.2, U2.8
unnamed: R21.1, R22.1, U2.10
unnamed: R21.2, U2.6, U2.7
VCC: C11.1, C12.2, D4.2, R1.1, U1.16, U3.2

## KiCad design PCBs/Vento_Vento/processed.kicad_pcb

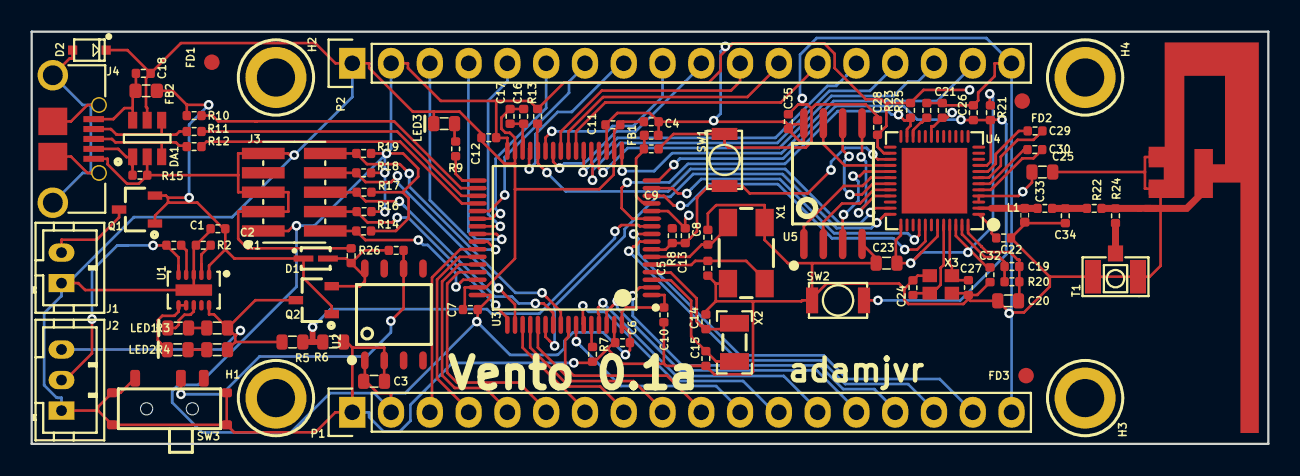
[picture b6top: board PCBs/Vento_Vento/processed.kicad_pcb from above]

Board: 4 copper layers, 81.0 x 27.0 mm, 97 parts (0 on the bottom side), 93 nets.

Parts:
ANT1: Inverted_F_PCB_Antenna; PCB_IF_ANT_2.4G
C1, C2: CL05A105KA5NQNC; C0402
C3, C23, C25: CL10A106KQ8NNNC; C0603
C4, C6, C7, C9, C10, C11, C12, C13, C17, C18, C21, C22, C26, C28, C32, C35: CL05B104JP5NNNC; C0402
C5, C8, C24, C27: CL05C090CB5NNNC; C0402
C14, C15: CL05C180GB5NCNC; C0402
C16: CL05A475KQ5NRNC; C0402
C19: GRM1557U1A302JA01D; C0402
C20: C0603C103J5JAC7867; C0603
C29, C30: GRM1555C1H271FA01D; C0402
C33: 600L3R9BT200T; C0402
C34: 600L2R4BT200T; C0402
D1: BAT20JFILM
D2: RSB39VTE-17
DA1: ESDA6V1BC6
FB1: BLM15HG601SN1D
FB2: MI0603K300R-10
FD1, FD2, FD3: FIDUCIAL
H1, H2, H3, H4: M2.5_Hole; M2.5_HOLE
J1: B2B-PH-K-S(LF)(SN)
J2: B3B-PH-K-S(LF)(SN)
J3: 20021121-00010C4LF
J4: 0475890001-MicroUSBPort; 0475890001
L1: 744901027; BLM15HG601SN1D
LED1: LTST-C191KGKT; LED0603
LED2: LTST-C191KFKT; LED0603
LED3: LTST-C193TBKT-5A; LED0603
P1, P2: CONN_01X18; Socket_Strip_Straight_1x18
Q1, Q2: DMG2307L-7
R1: RC1005F4870CS; R0402
R2, R8, R9, R14, R16, R17, R18, R19: RC1005F102CS; R0402
R3, R4: RC1608J202CS; R0603
R5, R6: ERA-3AEB3741V; R0603
R7, R10, R13, R21, R23, R25, R26: RC1005F103CS; R0402
R11, R12: CPF0402B22RE1; R0402
R15: RC1005J473CS; R0402
R20: RC1005F203CS; R0402
R22, R24: ERJ-2GE0R00X; R0402
SW1, SW2: B3U-1000P
SW3: CUS-12TB
T1: 1909763-1
U1: BQ24210DQCT; BQ24210
U2: TC1265-3.3VOA
U3: STM32F446RET6_-_TQFP64; STM32F446RET6
U4: ESP32
U5: W25Q64FWSSIG
X1: ABM3B8.000MHZB2T
X2: ABS07-32.768KHZ-9-T
X3: FA-128_26.0000MF10Z-AC3

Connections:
+3V3: C3.1, C4.1, C6.1, C7.1, C10.1, C11.1, C12.1, C21.1, C22.1, C23.1, C25.1, C28.1, C32.1, C35.1, FB1.1, J3.1, P1.2, P2.2, R13.1, R14.1, R16.1, R17.1, R18.1, R19.1, R21.1, R23.1, U2.1, U3.1, U3.19, U3.32, U3.48, U3.64, U4.1, U4.3, U4.4, U4.19, U4.26, U4.37, U4.43, U4.46, U5.8
/MCU_STM32F446RET6/BAT_VOLT: R5.2, R6.1, U3.10
/MCU_STM32F446RET6/ESPTOST_BOOT0: U3.54, U4.36
/MCU_STM32F446RET6/ESPTOST_BOOT1: R13.2, U3.28, U4.35
/MCU_STM32F446RET6/ESP_PGM_MODE: R23.2, U3.11, U4.23
/MCU_STM32F446RET6/ESP_ST_RST: C13.1, R8.2, SW1.1, U3.7, U4.27
/MCU_STM32F446RET6/ESP_URX: U3.14, U4.41
/MCU_STM32F446RET6/ESP_UTX: U3.15, U4.40
/MCU_STM32F446RET6/HEARTBEAT: R9.1, U3.33
/MCU_STM32F446RET6/NJTRST: J3.10, R19.2, U3.56
/MCU_STM32F446RET6/PA3: P2.17, U3.17
/MCU_STM32F446RET6/PA4: P2.16, U3.20
/MCU_STM32F446RET6/PA5: P2.15, U3.21
/MCU_STM32F446RET6/PA6: P2.14, U3.22
/MCU_STM32F446RET6/PA7: P2.13, U3.23
/MCU_STM32F446RET6/PA8: P2.3, U3.41
/MCU_STM32F446RET6/PA9: P1.3, U3.42
/MCU_STM32F446RET6/PA10: P1.4, U3.43
/MCU_STM32F446RET6/PA11: P1.5, U3.44
/MCU_STM32F446RET6/PA12: P1.6, U3.45
/MCU_STM32F446RET6/PB0: P2.10, U3.26
/MCU_STM32F446RET6/PB1: P2.9, U3.27
/MCU_STM32F446RET6/PB5: P1.10, U3.57
/MCU_STM32F446RET6/PB6: P1.11, U3.58
/MCU_STM32F446RET6/PB7: P1.12, U3.59
/MCU_STM32F446RET6/PB8: P1.13, U3.61
/MCU_STM32F446RET6/PB9: P1.14, U3.62
/MCU_STM32F446RET6/PB10: P2.8, U3.29
/MCU_STM32F446RET6/PC0: P1.16, U3.8
/MCU_STM32F446RET6/PC1: P1.17, U3.9
/MCU_STM32F446RET6/PC4: P2.12, U3.24
/MCU_STM32F446RET6/PC5: P2.11, U3.25
/MCU_STM32F446RET6/PC6: P2.7, U3.37
/MCU_STM32F446RET6/PC7: P2.6, U3.38
/MCU_STM32F446RET6/PC8: P2.5, U3.39
/MCU_STM32F446RET6/PC9: P2.4, U3.40
/MCU_STM32F446RET6/PC10: P1.7, U3.51
/MCU_STM32F446RET6/PC11: P1.8, U3.52
/MCU_STM32F446RET6/PC12: P1.9, U3.53
/MCU_STM32F446RET6/PC13: P1.15, U3.2
/MCU_STM32F446RET6/STM_ESP_RST: C26.1, R21.2, SW2.2, U3.16, U4.9
/MCU_STM32F446RET6/SWCLK_TCK: J3.4, R16.2, U3.49
/MCU_STM32F446RET6/SWDIO_TMS: J3.2, R14.2, U3.46
/MCU_STM32F446RET6/SWO_TDI: J3.8, R18.2, U3.50
/MCU_STM32F446RET6/SWO_TDO: J3.6, R17.2, U3.55
/MCU_STM32F446RET6/VBUS: C1.1, D1.1, FB2.1, Q1.1, Q1.2, Q2.1, R10.2, U1.1
/Power/BAT: J2.3, Q2.3, R3.2, R4.2, R5.1, U1.10
/Power/LDO_VIN: C2.1, D1.2, Q2.2, R26.1, U2.8
/Power/THERM: J2.2, R2.2, U1.5
/WiFi_BLE_ESP32/ANT: C33.2, C34.1, R22.1
/WiFi_BLE_ESP32/ANT_IF: ANT1.1, R22.2, R24.1
/WiFi_BLE_ESP32/ANT_UM: R24.2, T1.1
/WiFi_BLE_ESP32/CLK: U4.31, U5.6
/WiFi_BLE_ESP32/CS: U4.30, U5.1
/WiFi_BLE_ESP32/LNA: C33.1, L1.1, U4.2
/WiFi_BLE_ESP32/SD1: U4.33, U5.5
/WiFi_BLE_ESP32/SD2: U4.28, U5.7
/WiFi_BLE_ESP32/SD3: U4.29, U5.3
/WiFi_BLE_ESP32/SDO: U4.32, U5.2
GND: ANT1.2, C1.2, C2.2, C3.2, C4.2, C5.2, C6.2, C7.2, C8.2, C9.2, C10.2, C11.2, C12.2, C13.2, C14.2, C15.2, C16.2, C17.2, C18.1, C20.2, C21.2, C22.2, C23.2, C24.2, C25.2, C26.2, C27.2, C28.2, C32.2, C34.2, C35.2, D2.2, DA1.2, DA1.5, J1.1, J2.1, J3.3, J3.5, J3.9, J4.5, L1.2, LED3.2, P1.1, P1.18, P2.1, P2.18, R1.2, R6.2, R7.2, R15.2, R25.1, SW1.2, SW2.1, SW3.1, SW3.4, T1.2, U1.3, U1.11, U2.2, U3.12, U3.18, U3.31, U3.47, U3.63, U5.4, X1.2, X1.4, X3.2, X3.4
unnamed: C5.1, U3.5, X1.1
unnamed: C8.1, U3.6, X1.3
unnamed: C9.1, FB1.2, U3.13
unnamed: C14.1, U3.4, X2.1
unnamed: C15.1, U3.3, X2.2
unnamed: C16.1, C17.1, U3.30
unnamed: C18.2, DA1.6, FB2.2, J4.1
unnamed: C19.1, R20.1, U4.47
unnamed: C19.2, C20.1, R20.2, U4.48
unnamed: C24.1, U4.44, X3.1
unnamed: C27.1, U4.45, X3.3
unnamed: C29.1, U4.7
unnamed: C29.2, U4.8
unnamed: C30.1, U4.5
unnamed: C30.2, U4.6
unnamed: D2.1, J4.6, J4.7, J4.8, J4.9, J4.10, J4.11
unnamed: DA1.1, J4.4, R15.1
unnamed: DA1.3, J4.3, R12.2
unnamed: DA1.4, J4.2, R11.2
unnamed: J1.2, Q1.3
unnamed: LED1.1, R3.1
unnamed: LED1.2, U1.8
unnamed: LED2.1, R4.1
unnamed: LED2.2, U1.6, U1.7
unnamed: LED3.1, R9.2
unnamed: R1.1, U1.2
unnamed: R2.1, U1.4
unnamed: R7.1, U3.60
unnamed: R10.1, U3.34
unnamed: R11.1, U3.35
unnamed: R12.1, U3.36
unnamed: R25.2, U4.22
unnamed: R26.2, SW3.2, U2.6

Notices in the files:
PCBs/VC4000MultiROM_MultiRomCard/processed.kicad_pcb:
© 2015/16
